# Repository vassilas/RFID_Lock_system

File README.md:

# RFID Lock System

The main Goal of this project it to develop a system whick cotrols a door-lock with a relay.
To unlock the door successfully you need to place three different RFID tags in
specific rfid reader's potitions . 

## Getting Started

The wirign is described in the source code (<project_folder>/src) 
Serial Monitor is used for testing the status of the system .

### Prerequisites

What things you need to install the software and how to install them

```
1) Arduino IDE
2) AddicoreRFID library
3) RFID livrary
```
## Schematic Image

## Layout Image

## Some usefull links

* https://www.addicore.com/RFID-AddiKit-p/126.htm - RFID AddiKit with RC522

## Future plans

1. Extend the range of RFID reader 
2. Add tow more RFID readers 
3. power the relay only when specific RFID tags are present

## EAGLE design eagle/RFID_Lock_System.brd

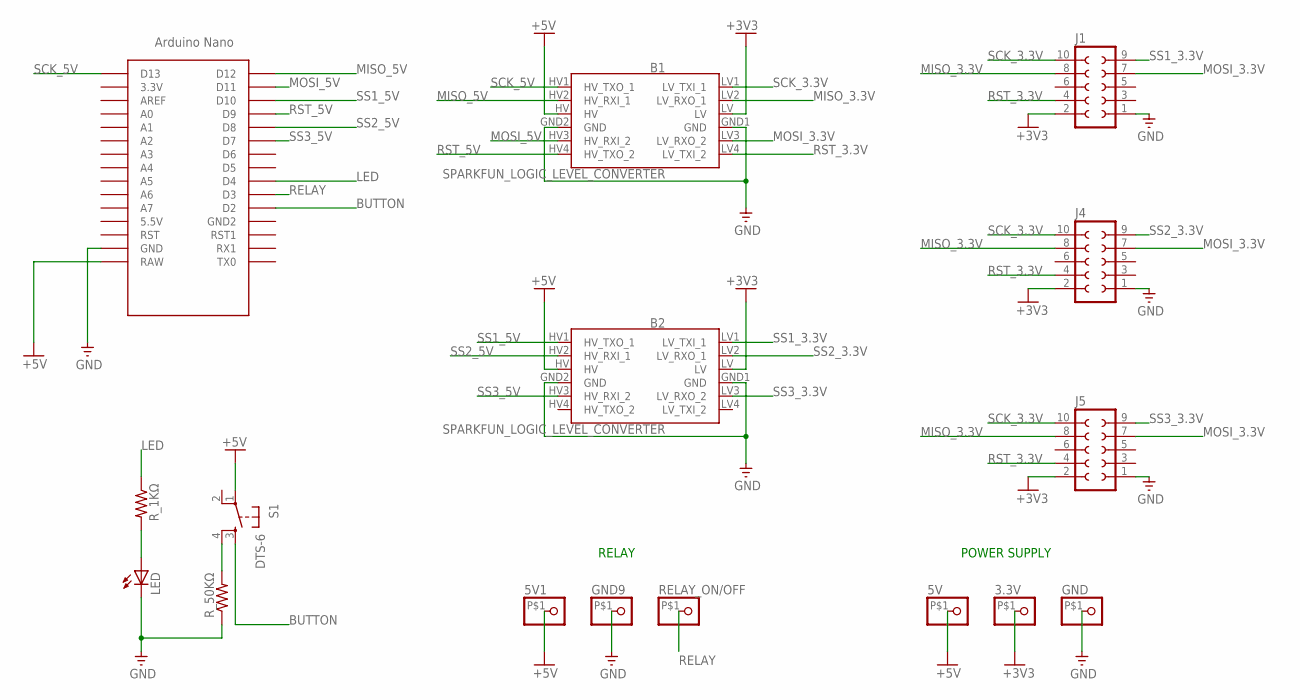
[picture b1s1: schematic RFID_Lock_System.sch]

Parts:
3.3V, 5V, 5V1: PINHD-1X1-BIGPOGO; 1X1-BIGPOGO
B1, B2: SPARKFUN_LOGIC_LEVEL_CONVERTER
GND, GND9: PINHD-1X1-BIGPOGO; 1X1-BIGPOGO
J1, J4, J5: SOCKET-10V; S10V
LED: LED5MM
RELAY_ON/OFF: PINHD-1X1-BIGPOGO; 1X1-BIGPOGO
R_1KΩ, R_50KΩ: R-US_0204/7; 0204/7
S1: DTS-6; MPN MC32829
U$1: NANO

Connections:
+3V3: 3.3V.P$1, B1.LV, B2.LV, J1.2, J4.2, J5.2
+5V: 5V.P$1, 5V1.P$1, B1.HV, B2.HV, S1.1, U$1.RAW
BUTTON: S1.3, U$1.D2
GND: B1.GND1 (GND), B1.GND2 (GND), B2.GND1 (GND), B2.GND2 (GND), GND.P$1, GND9.P$1, J1.1, J4.1, J5.1, LED.K (C), R_50KΩ.1, U$1.GND
LED: R_1KΩ.1, U$1.D4
MISO_3.3V: B1.LV2 (LV_RXO_1), J1.8, J4.8, J5.8
MISO_5V: B1.HV2 (HV_RXI_1), U$1.D12
MOSI_3.3V: B1.LV3 (LV_RXO_2), J1.7, J4.7, J5.7
MOSI_5V: B1.HV3 (HV_RXI_2), U$1.D11
unnamed: LED.A, R_1KΩ.2
unnamed: R_50KΩ.2, S1.4
RELAY: RELAY_ON/OFF.P$1, U$1.D3
RST_3.3V: B1.LV4 (LV_TXI_2), J1.4, J4.4, J5.4
RST_5V: B1.HV4 (HV_TXO_2), U$1.D9
SCK_3.3V: B1.LV1 (LV_TXI_1), J1.10, J4.10, J5.10
SCK_5V: B1.HV1 (HV_TXO_1), U$1.D13
SS1_3.3V: B2.LV1 (LV_TXI_1), J1.9
SS1_5V: B2.HV1 (HV_TXO_1), U$1.D10
SS2_3.3V: B2.LV2 (LV_RXO_1), J4.9
SS2_5V: B2.HV2 (HV_RXI_1), U$1.D8
SS3_3.3V: B2.LV3 (LV_RXO_2), J5.9
SS3_5V: B2.HV3 (HV_RXI_2), U$1.D7

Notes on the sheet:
POWER SUPPLY
RELAY

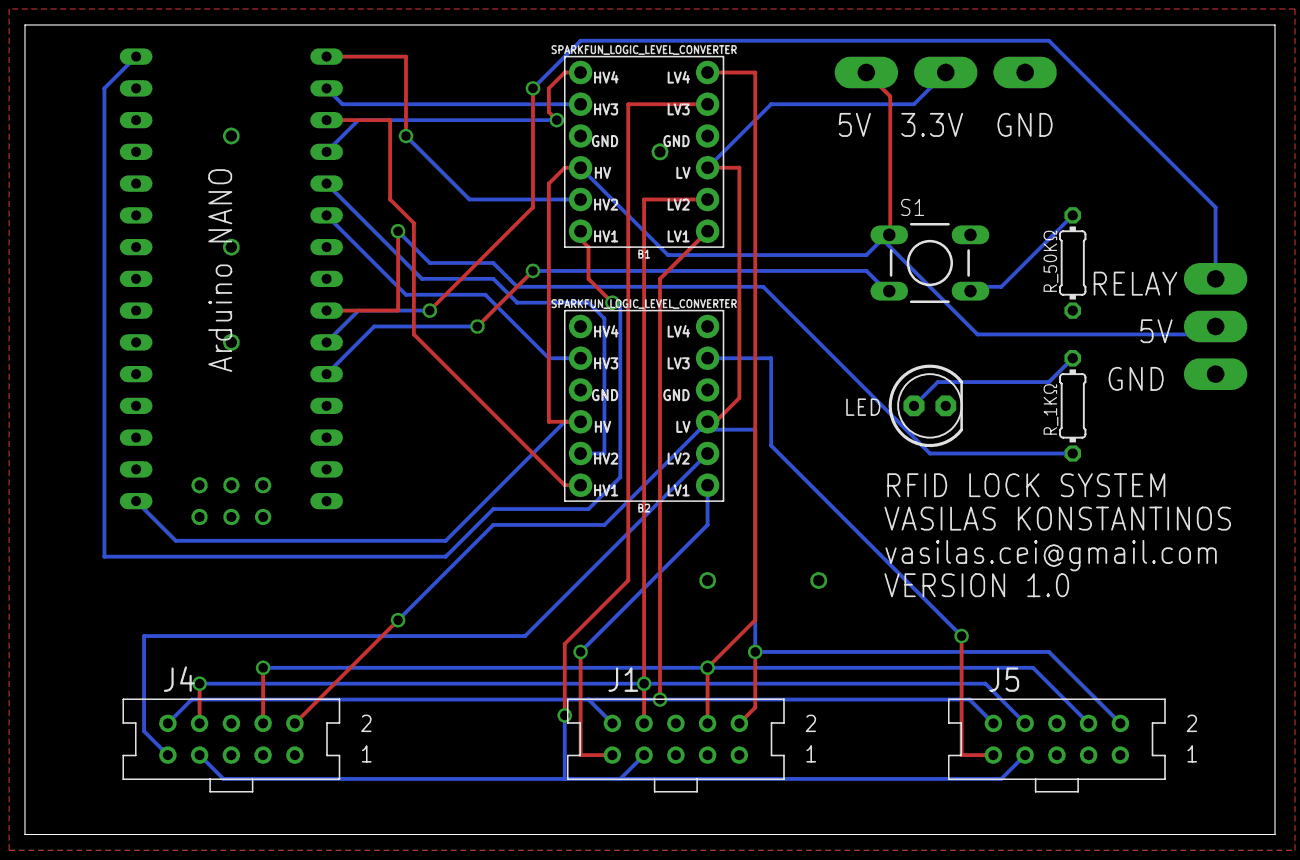
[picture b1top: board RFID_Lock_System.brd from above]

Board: 2 copper layers, 100.0 x 64.8 mm, 16 parts (0 on the bottom side), 22 nets.

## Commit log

2017-09-14 Lcd Test code git add src/Lock_System/Lock_System.ino !
2017-09-14 [SW] Recognize Presence of a RFID Tag - Print status to LCD
2017-09-15 [SW] Display RFID tag_code to LCD
2017-09-15 File management - organization
2017-09-15 [SW] Include Relay control . The relay status change when a RFID tag is recognized
2017-09-15 Some usefull documentations , links and references for the project
2017-09-15 Initialize Schematic with Eagle
2017-09-15 [SW] Save last RFID Tag's id readed into EEPROM of the AVR and print it on restart/start-up
2017-09-15 [SW] Register a button to togle the state of the relay
2017-09-15 Update README file with Future plans sector
2017-09-18 [SW] Use another library for future support of three rfid reader modules without multiplexer
2017-09-18 [SW] Add a function wich takes a argument for reading a specific rfid and returns the status and read value
2017-09-18 [SW] Add support for relay control , and button
2017-09-20 [SW] Adding three modules RC522 on a single Arduino UNO , Using MFRC522.h Library
2017-09-20 [SW] Add EEPROM support , when a RFID-Reader scans a card , the card_id is saved in eeprom memory
2017-09-21 [SW] Add a button , its' function : When it's pressed rfid tags are saved in EEPROM
2017-09-23 [SW] Complete the Lock System by checking the TAGS , if each reader scan the valid tag => Unlock state
2017-09-27 [SW] Proper read from the tags . In each cycle each reader get tow requests , This is sovling the synchronization issue due to rfid-read after the recognition of a tag follows a non-pressented tag cy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
2017-09-27 [SW] Add debug mode with serial monitoring the states of the system, Re-order led control with relay control
2017-10-05 Added Diagram.xml
2017-10-13 Add eagle schematic and PCB files
2017-10-13 Some clean-up and upload Gallery Folder with images
2017-10-13 Upload Image
2017-11-12 Update gallery with pcb layouts , update private section with some architecture schematics
2017-11-12 Update README file
2017-11-12 Update README , Update eagle project file
2017-12-02 Update SW , some modifications for the relay control , and Links text file

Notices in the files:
parts and their libraries:
SparkFun-Boards: Licensing: Creative Commons ShareAlike 4.0 International - https://creativecommons.org/licenses/by-sa/4.0
supply0: Copyright (C) 2007, Bob Starr
